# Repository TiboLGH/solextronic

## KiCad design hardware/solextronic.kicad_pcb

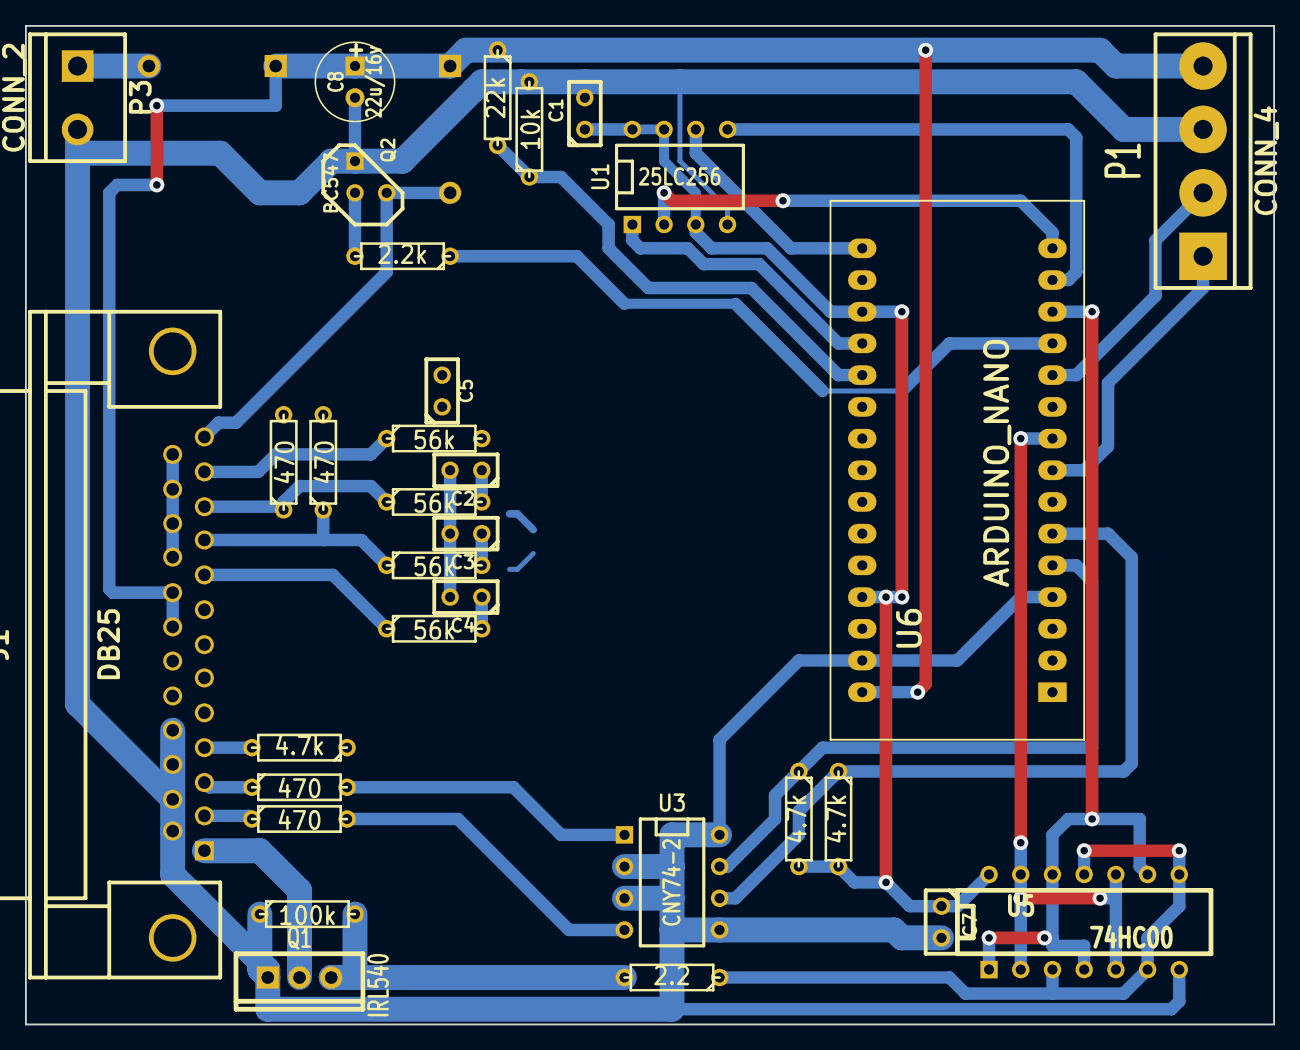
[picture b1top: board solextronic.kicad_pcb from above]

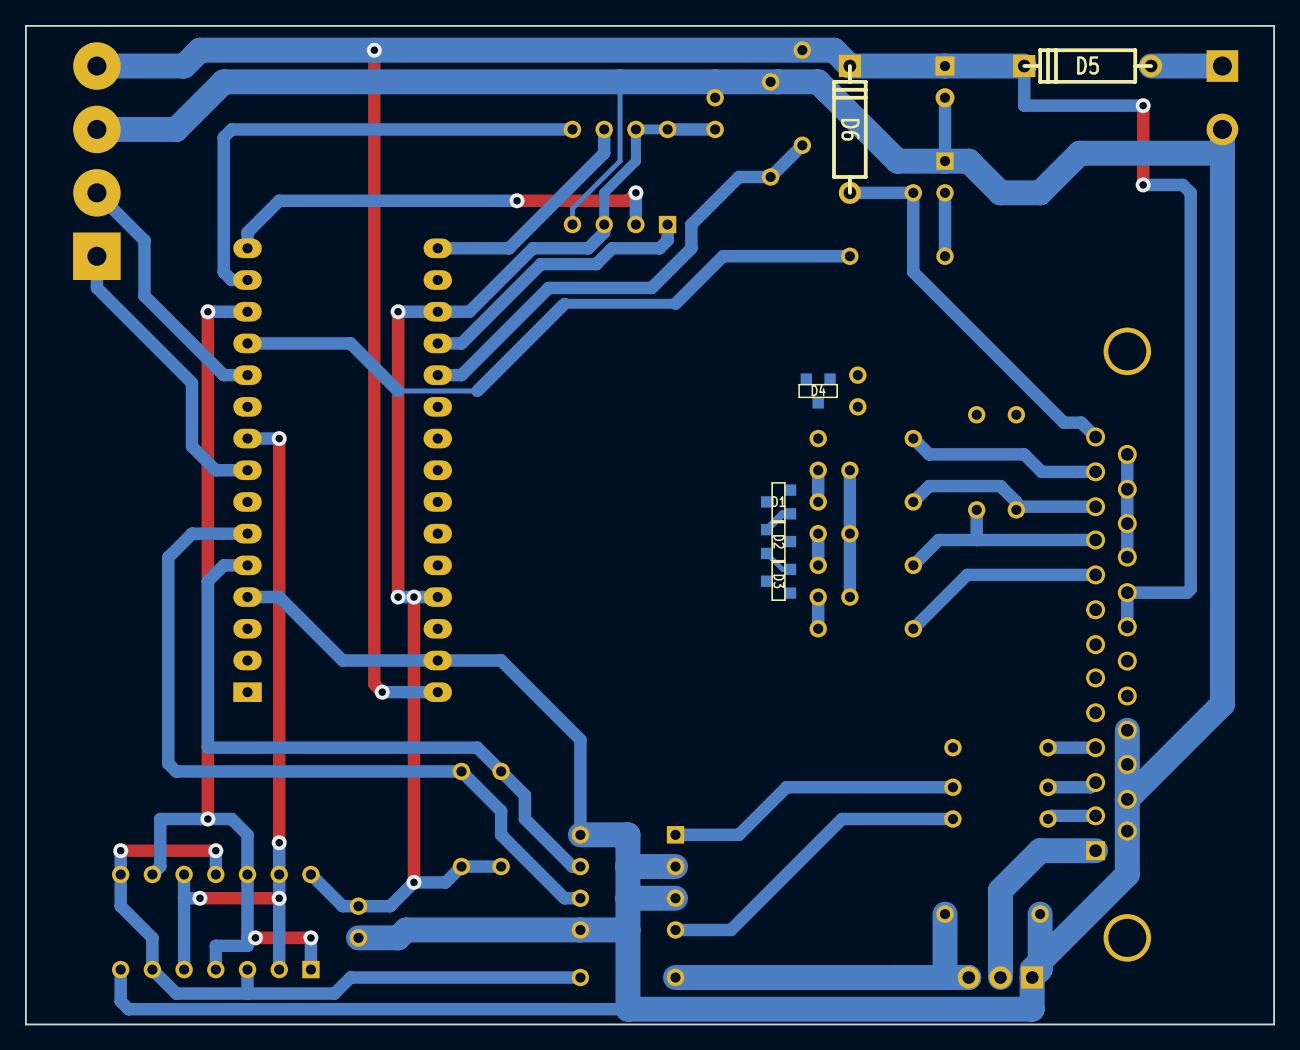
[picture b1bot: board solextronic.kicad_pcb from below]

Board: 2 copper layers, 100.0 x 80.0 mm, 38 parts (6 on the bottom side), 37 nets.

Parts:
C1, C2, C3, C4, C5, C7: 100nF; C1
C8: 22u/16v; C1V7
D1, D2, D3, D4: BAT54S; ST23AK#1
D5, D6: 1N4007; D4
J1: DB25; DB25FC
P1: CONN_4; bornier4
P3: CONN_2; bornier2
Q1: IRL540; TO220_VERT_GDS
Q2: BC547; TO92-EBC
R1, R3, R4, R16: 56k; R3
R2, R5, R6, R15: 470; R3
R7, R8, R11: 4.7k; R3
R9: 2.2; R3
R10: 100k; R3
R12: 22k; R3
R13: 10k; R3
R14: 2.2k; R3
U1: 25LC256; DIP-8__300
U3: CNY74-2; DIP-8__300
U5: 74HC00; DIP-14__300
U6: ARDUINO_NANO; arduino_nano

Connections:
+5V: C1.1, C7.1, D1.3, D2.3, D3.3, D4.3, J1.22, J1.23, J1.24, J1.25, R2.2, R7.2, R8.2, R11.1, R15.2, U1.3, U1.7, U1.8, U5.14, U6.18, U6.27
+BATT: C8.1, D5.2, D6.2, J1.20, J1.21, P1.4, R12.1, U6.30
/AUX1: J1.5, U6.10
/BTN1: J1.4, R11.2, U6.7
/CLT: J1.11, R1.1, R15.1
/CLTAdc: C2.1, D1.2, R1.2, U6.22
/CMD_INJ: U5.1, U5.4, U5.9, U5.12, U6.13
/EnableHV: P1.1, U6.8
/FP_CLK: J1.7, U6.24
/FP_DATA: J1.8, U6.23
/IAT: J1.10, R2.1, R3.1
/IATAdc: C3.1, D2.2, R3.2, U6.25
/Ignition: J1.6, P1.2, U6.11
/Injection: J1.1, Q1.D
/MAP: J1.9, R4.1
/MAPAdc: C4.1, D3.2, R4.2, U6.26
/MISO: U1.2, U6.15
/MOSI: U1.5, U6.14
/Motor: R8.1, U3.7, U6.5
/PUMP: D6.1, J1.13, Q2.C
/PUMP_CMD: R14.1, U6.12
/PWM_INJ: U5.2, U5.5, U5.10, U5.13, U6.9
/SCK: U1.6, U6.16
/SS: U1.1, U6.19
/TPS: J1.12, R16.1
/TPSAdc: C5.1, D4.2, R16.2, U6.21
/TopMotor: J1.3, R6.1
/TopWheel: J1.2, R5.1
/Vbat: R12.2, R13.1, U6.20
/Wheel: R7.1, U3.6, U6.6
GND: C1.2, C2.2, C3.2, C4.2, C5.2, C7.2, C8.2, D1.1, D2.1, D3.1, D4.1, J1.14, J1.15, J1.16, J1.17, P1.3, P3.2, Q1.S, Q2.E, R10.1, R13.2, U1.4, U3.2, U3.3, U3.5, U3.8, U5.7, U6.4, U6.29
unnamed: R9.1, U5.3, U5.6, U5.8, U5.11
unnamed: R6.2, U3.1
unnamed: D5.1, P3.1
unnamed: Q2.B, R14.2
unnamed: R5.2, U3.4
unnamed: Q1.G, R9.2, R10.2

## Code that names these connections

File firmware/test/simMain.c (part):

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
enum {IAT = 0, CLT};

static float TempToVoltage(const float degree, int type, eeprom_data_t *eData) // 0 IAT, 1 CLT
{
    // Reverse table to get adc value vs temp
    volatile u8 tempTable[TABSIZE][2];
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    return voltage;
}

static float ThrToVoltage(const float TPS, eeprom_data_t *eData) // TPS in %
{
    // note that TPS min and max are in ADC unit, not in %
    float adc = (eData->tpsMax - eData->tpsMin) * TPS / 100. + eData->tpsMin;
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    
    if(buf) // for pretty print
    {
        snprintf(buf, 256, "Led %s, Aux %s, Inj %s, Ign %s, Pump %s, HV %s", state.ledPin?"ON":"OFF",
                                                                             state.auxPin?"ON":"OFF",
                                                                             state.injPin?"ON":"OFF",
                                                                             state.ignPin?"ON":"OFF",
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                                        {120, 120, 30, 90,  90},
                                        {150, 180, 35, 100, 100}}; // battery, CLT, IAT, TPS, MAP

    const float analogMax[5] = { 150, 150, 40,  100, 110}; // battery, CLT, IAT, TPS, MAP
    current_data_t gState;
    // Update config
    eeprom_data_t eDataToWrite;
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    CHECK_AND_PRINT(gState.speed,0, 1,      "Speed   : %4dkm/h | %4dkm/h | %5.1f \n");
    CHECK_STATE_AND_PRINT(gState.engineState, 0x0);

    // Pump (PD7), HV (PD5), ignition (PB1), injector (PB2) states : they shall be off
    output_t state = GetOutputState(NULL);
    CHECK_PIN_AND_PRINT(state.pumpPin, 0, "Pump      : %s\n");
    CHECK_PIN_AND_PRINT(state.hvPin,   0, "HV        : %s\n");
    CHECK_PIN_AND_PRINT(state.ignPin,  0, "Ignition  : %s\n");
    CHECK_PIN_AND_PRINT(state.injPin,  0, "Injection : %s\n");
   
    if(verdict == FAIL) return verdict; 

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    QueryState(&uart_com, &gState);
    CHECK_STATE_AND_PRINT(gState.engineState, 0x1);
    state = GetOutputState(NULL);
    CHECK_PIN_AND_PRINT(state.pumpPin, 1, "Pump      : %s\n");
    CHECK_PIN_AND_PRINT(state.hvPin,   1, "HV        : %s\n");
    timing_analyzer_reset(&timing_analyzer_ignition, 5);
    timing_analyzer_reset(&timing_analyzer_injection, 5);
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
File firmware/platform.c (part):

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    /*
     * PORT B :
     *  Aux on PB0 : input
     *  Ignition on PB1 : output
     *  Injection on PB2 : output
     *  LED on PB5 : output
     * Port D :
     *  Dead high on PD2/INT0 : input, pull-up, interrupt on rising edge
     *  Wheel synchro on PD3/INT1 : input, pull-up, interrupt on rising edge 
     *  BTN1/Cranking on PD4 : input, pull-up 
     *  HV supply on PD5 : output
     *  Pump on PD7 : output
     */

    DDRB  = 0b00100110;
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            IGN_INT_DISABLE;
            curIgnTiming.start = TCNT1 + nextIgnTiming.start;
            curIgnTiming.duration  = nextIgnTiming.duration;
            PIN_OFF(IGNITION_PIN, eData.ignPolarity);
            curIgnTiming.state = OFF;
            OCR1A = curIgnTiming.start;
            IGN_INT_ENABLE;
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{
    if(curIgnTiming.state == OFF)
    {
        PIN_ON(IGNITION_PIN, eData.ignPolarity);
        curIgnTiming.state = ON;
        OCR1A += curIgnTiming.duration;
    }else{
        PIN_OFF(IGNITION_PIN, eData.ignPolarity);
        curIgnTiming.state = OFF;
        if(curIgnTiming.pending) {
            curIgnTiming.pending = 0;
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    gState.CLT = Interp1D(eData.cltCal, gState.rawClt);     
    gState.IAT = Interp1D(eData.iatCal, gState.rawIat); 
    if(gState.rawTps <= eData.tpsMin) 
        gState.TPS = 0; 
    else if(gState.rawTps >= eData.tpsMax) 
        gState.TPS = 100;
    else
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
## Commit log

2012-10-13 initial empty check-in
2012-10-13 Specifications principales
2012-10-21 Ajout des pages liens et toDo List
2012-10-21 Makefile issue de OpenSilicium #2
2012-10-23 Qques liens de plus
2012-10-23 1er main, simple echo UART 57600
2012-10-24 Ajout cible tags
2012-11-04 Ajout lien vers page d'accueil
2012-11-04 Page wiki sur le schema : Tableau d'affectation des broches Arduino
2012-11-04 Debut section FlyBack
2012-11-18 Revision de la roadmap
2012-11-18 Service timer software + interpreteur de commande basique
2013-01-15 Support des acquisitions analogiques
2013-01-17 integration revision fossil dans le numero de version
2013-06-16 DOC - Ajout du signal de rotation de la roue
2013-06-23 DOC - Affectation des ADC
2013-06-23 Gestion PWM alimentation HT et boucle d'asservissement
2013-06-29 SIMU - 1er commit
2013-07-01 FW - arguments de sendToUart...
2013-07-02 FW - Declenchement de l'envoie du buffer TX
2013-07-02 SIM - Ajout des parts pulse_input et UART
2013-07-07 SIM - Ajout des options de la ligne de commande + makefile simulation
2013-07-10 FW - Mesure de du regime
2013-07-10 FW - Mesure de la vitesse
2013-07-13 SIM - Ajout des composants analog, timing analyzer et HT_supply
2013-07-13 DOC - Ajout de la page simulation
2013-07-14 DOC - Ajout du schema bloc
2013-07-14 HW - Fichiers schema (vide)
2013-07-14 FW - Ajout des licenses
2013-07-18 DOC - Ajout PWM injecteur
2013-07-19 SIM - Ajout des entrees analogiques
2013-07-19 DOC - Ajout entree capteur roue sur faisceau
2013-07-19 DOC - Clean de l'accueil
2013-07-27 SIM - Tests version, RPM et vitesse
2013-07-28 DOC - Mise a jour des commandes
2013-07-28 FW - Commande set general
2013-07-30 FW - Gestion de l'EEPROM
2013-09-22 FW - fix sur la mesure de basses vitesses
2013-10-15 DOC - Add README file
2013-10-21 DOC - Suppression de la doc dans le repo principal. Tout est dans solextronic.wiki
2013-11-01 FW - Gestion des ADC + tests en simu. Conversions faites en tache de fond, next step les passer sous interruption
2013-11-01 FW - Changement du numero de version de Fossil a Git
2013-11-02 FW - Ajout des commandes injection et allumage
2013-11-04 FW - Initialisation de l'EEPROM depuis la flash
2013-11-04 FW - Define pour les feignassses
2013-11-04 FW - Fix sur l'initialisation de l'EEPROM. Tests OK
2013-11-11 HW - Schema de la carte de test externe
2013-11-11 HW - PDF et png du schema de la testboard
2013-11-19 COMP - commit initial du calculateur de timings injection et allumage
2013-11-21 COMPUTATION - Correction du makefile
2013-11-24 SCH - Debut schema de la carte principale. Modification du faisceau et de la carte de test
2013-11-24 FW - changement de l'entree ADC pour la batterie. Attention, bug detecte dans simavr sur l'ADC7...
2013-12-03 COMPUTATION - lecture des tables d'allumage et d'injection
2013-12-03 HW - Mise a jour du schema de la carte principale
2013-12-04 FW - Issue 1 : gestion des assert. Sortie sur le port serie
2013-12-05 COMPUTATION - traduction des commentaires en francais : les commentaires du code permettront de generer la doc
2013-12-09 MODEL - Renommage en model (plus parlant et logique, au moins pour moi)
2013-12-09 MODEL - renommage du repertoire
2013-12-17 FW - Mise a jour de la variable d'etat interne. Va servir de base pour l'integration avec TunerStudio
2013-12-19 FW - Modifications pour supporter le protocole serie de TunerStudio
2013-12-29 FW - Integration avec Tunerstudio. Attention simulation HS
2014-01-01 SIM - Adaptation des tests de simu au nouveau protocole serie
2014-01-02 MODEL - mode de calcul du debit d'injecteur
2014-01-02 TUNER - Version initial du fichier de configuration de TunerStudio
2014-03-10 Model - calcul du timing d'allumage
2014-03-12 FW - ajout gestion des signaux allumage et injection
2014-03-12 FW - Test : mode verbose, debut du test injection, provision de l'ensemble des tests
2014-03-13 FW - un peu de menage
2014-03-16 SCH - Passage au DB25
2014-03-16 SCH - script pour convertir les schemas en png et pdf et resultats
2014-04-20 HW - Ajout Alimemtation HT et controle de l'allumage
2014-04-20 HW - Sorties PNG et PDF de l'alimentation HT
2014-04-21 HW - PCB du bloc CDI
2014-06-16 FW - Mode de test injection : banc de test (partie 1)
2014-06-22 FW - Ajout mode de test injection
2014-06-30 FW - Ajout du mode test d'allumage : allumage toutes les 10ms
2014-07-01 TEST - Ajout du parametre retry pour relancer les tests fail. Utile pour les campagnes auto, la liaison serie virtuelle est parfois instable
2014-07-01 TEST - Typo sur le code de retry
2014-07-26 FW : support de la table d'avance a l'allumage. Attention, le support du timing d'injection est casse
2014-07-27 FW : conversion de l'injection au timer1 free-running
2014-08-05 HW - Modification de la taille du bloc CDI pour passer dans un format 60 x 100mm
2014-11-02 [SIM] Retry sur les ecritures UART
2014-11-02 HW - 1er jet du PCB principal. Attention, modification du pinout des connecteurs
2014-11-08 FW - amelioration de Mr Propre
2014-11-25 Adaptation du makefile pour simAvr (a revoir) et fix sur les retry
2014-12-02 HW - Renommage des signaux et mise à jour carte de test
2014-12-04 FW - Changement des noms des signaux de temperature/pression/accelerateur
2014-12-09 HW - Modification du pinout connecteur CDI. Attention PCB pas a jour !
2014-12-09 HW - Debut optim carte principale
2014-12-09 HW - Modification du pinout connecteur CDI : Mise a jour PCB
2014-12-12 HW - Simplification des entrees
2014-12-13 SIM - SleepMs est maintenant sysnchronise avec la simulation
2014-12-13 SIM - Typo dans le test RPM
2015-01-04 FW - Gestion du LCD/bouton : 1ere squelette
2015-02-11 FW - la version dans la signature est lue depuis le fichierversion
2015-02-16 TEST - Issue 7 : script de tests automatique. A deployer sur un serveur d'integration continue du pauvre
2015-02-17 FW - Correction sur l'affichage de la version
2015-02-27 FW - LCD/boutons : 2e commit, work in progress
2015-03-01 FW - Gestion des conversions ADC. A tester
2015-03-16 HW - Ajout alimention variable sur la carte de test
2015-03-29 FW - LCD/boutons 3e partie - work in progress
2015-03-29 HW - mise a jour du schema principale : simplification pour supprimer le bluetooth
2015-03-29 Migrating wiki contents from Google Code
2015-03-29 README a la sauce GitHub
2015-03-29 Avec le bon nom
2015-04-08 HW - Mise a jour de la carte de test
2015-04-24 FW : Script de mise a jour automatique des fichiers documentation et tuner studio a partir de vardef.h. Part 1
2015-04-28 HW - testboard : code du PIC
2015-04-28 HW - testBoard ajout du PIC
2015-04-30 FW : Script de mise a jour automatique des fichiers documentation et tuner studio a partir de vardef.h. Part 2
2015-05-08 TestBoard - mise a jour schema et soft PICavec fix pour le pb de reentrance
2015-05-21 LCD - Correction driver LCD et menu
2015-05-21 FW - Ajout variable pour injection/allumage
2015-05-21 FW - Clean debug pour ne pas interferer avec l'I2C
2015-05-21 HW - Correction schema principal et carte stim pour avoir l'alim 12v
2015-05-24 FW - Ajuste messages sur le LCD
2015-05-24 FW - Remap des entrees ADC + argument pour les conversions
2015-05-24 FW - ADC correction gestion interruption, test OK
2015-06-05 FW - Ajout squelette du calcul d'injection
2015-06-05 FW - Ajout service chronometre : pas teste !
2015-06-14 HW - Testboard : changement LED de visu
2015-06-14 FW - Offset de 0.7v pour la tension batterie
2015-06-14 FW - Chrono : tests et fix mineur
2015-06-14 FW - Front panel : anti-rebond des btn
2015-06-22 FW - Gestion de l'inection/allumage au demarrage
2015-07-06 FW - issue #18 : gestion des min/max TPS
2015-07-06 FW - Initialisation des tables en EEPROM
2015-07-12 FW - issue #18 : detection ralenti/plein gaz
2015-07-12 FW - issue #21 : gestion de la pompe a essence
2015-07-12 HW - issue #9 : schema du faisceau
2015-07-12 README - mise a jour light de la page d'accueil
2015-07-12 FW - Issue #10 : gestion de la pompe a essence
2015-07-13 FW - issue #15 support partiel de l'alim HT
2015-07-15 SIM - reparation de la compil de la simu. Simu toujours cassee au passage
2015-07-19 FW / HW - Nettoyage de la gestion des IOs dans le FW et le schema
2015-07-27 FW - Facteur de correction sur la tension de la batterie
2015-07-27 FW - Modification des variables bitfield
2015-08-04 FW - Realignement avec Tunerstudio
2015-08-05 Version 0.2
2015-08-05 On attaque la version 0.3
2015-08-09 FW - Issue #26 : relecture de l'EEPROM au boot
2015-08-09 FW - Issue #25 : gestion du define SIM
2015-10-24 HW - Correction sur le generateur haute-tension. PCB a revoir
2015-11-22 FW - Calcul de l'injection, partie 1
2015-12-05 SIM - Nettoyage simulation : test vitesse/version OK, test RPM 50% OK, autres a reprendre
2015-12-07 SIM - Reparation du test des entrees analogiques
2015-12-19 SIM - Correction test RPM. Attention, necessite un patch sur simavr !
2016-01-24 SIM - Reparation test injection
2016-01-24 SIM - Reparation test allumage
2016-03-20 FW - Ajout test timing et model : modele simplifie, test non stable
2016-05-14 SIM - Ajout des rampes sur valeurs analogiques et pulses
2016-06-05 SIM - Issue #33 : fichiers VCD et CSV sur les structures eData et gState
2016-06-05 SIM : fichiers sim_helpers oublies : amelioration des fonctions de traces de simavr
2016-06-13 SIM - Issue #35 Gestion UART dans un thread separe. Fix sur le fichier VCD
2016-06-13 FW - Correction du champs _second_
2016-07-06 SIM - part 1 test starting
2016-09-18 SIM - Desactive les logs sur les traces VCD
2016-09-21 SIM - Part 1 du test starting : divers fix, amorce part 2
2016-09-21 SIM - correction sur le generateur de pulse en cas de stop/start
2016-09-22 SIM - Fix sur les variables bits pour le fichier de description
2016-10-16 SIM - Support des rampes sur les entrees analogiques
2016-10-16 SIM - Gestion de la polarite du push button
2016-10-16 FW - attente de 5 cycles avant de calculer un RPM
2016-12-14 SIM - Correction sur la gestion de rampe pulse input
2016-12-14 FW - Fix gestion du moteur cale
2016-12-14 SIM - Part 3 du test starting : divers fix
2016-12-27 SIM - Issue #37 : premier jet
2016-12-30 SIM - Issue #37 : ajout d'un module de log centralise. Push_button convertit, les autres a venir
2017-01-08 FW - Correction calcul injection - ajout gestion du temps d'injection au demarrage en fct de la temperature - correction des conversions injector rate
2017-01-08 Model - ajout spreadsheet de base
2020-04-19 SW - mise à jour en python3

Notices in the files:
firmware/platform.c:
Copyright (C) 2012 by Thibault Bouttevin
Solextronic is free software; you can redistribute it and/or modify
it under the terms of the GNU General Public License as published by
the Free Software Foundation; either version 3 of the License, or
any later version.
firmware/test/simMain.c:
Copyright (C) 2013 by Thibault Bouttevin
